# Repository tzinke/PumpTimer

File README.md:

<p>A timer for my pool pump using a Raspberry Pi Zero W and a custom-made PCB.</p>

# Pool Pump Timer Instructions

<p>This device emits its own wi-fi network which will allow you to connect to the controller and set schedules and toggle the pump on/off.</p>

<p>The name of the network is PumpController, and the password is PumpController2803Pool</p>
  
<p>This network is NOT connected to the internet, so you'll probably want to deselect auto-connect for this network (otherwise your device might automatically hop on this network and not be connected to the internet). To control the device, you will also need to turn cell data off if connecting with a phone.</p>

<p>Once connected, open a browser and navigate to pumpcontroller.com. This will pull up the controller interface.</p>

<p>Here, you can set a schedule to turn the pump on/off at the same time each day, set the on-board clock, set a "one-time run" (a schedule that will only execute a single time, after which the daily schedule will resume), toggle the pump on/off manually, and view logs from the last 3 months.
The on-board clock is very accurate with little drift, but it is not configured to automatically adjust for daylight savings.</p>

<p>The device is also configured to turn the pump on for at least 10 minutes if the temperature gets too close to 32F in order to prevent equipment damage from freezes.
The on-board temperature sensor isn't terribly accurate, so there is an adjustment factor that you can change to get it more accurate/modify the "freeze" threshold.</p>

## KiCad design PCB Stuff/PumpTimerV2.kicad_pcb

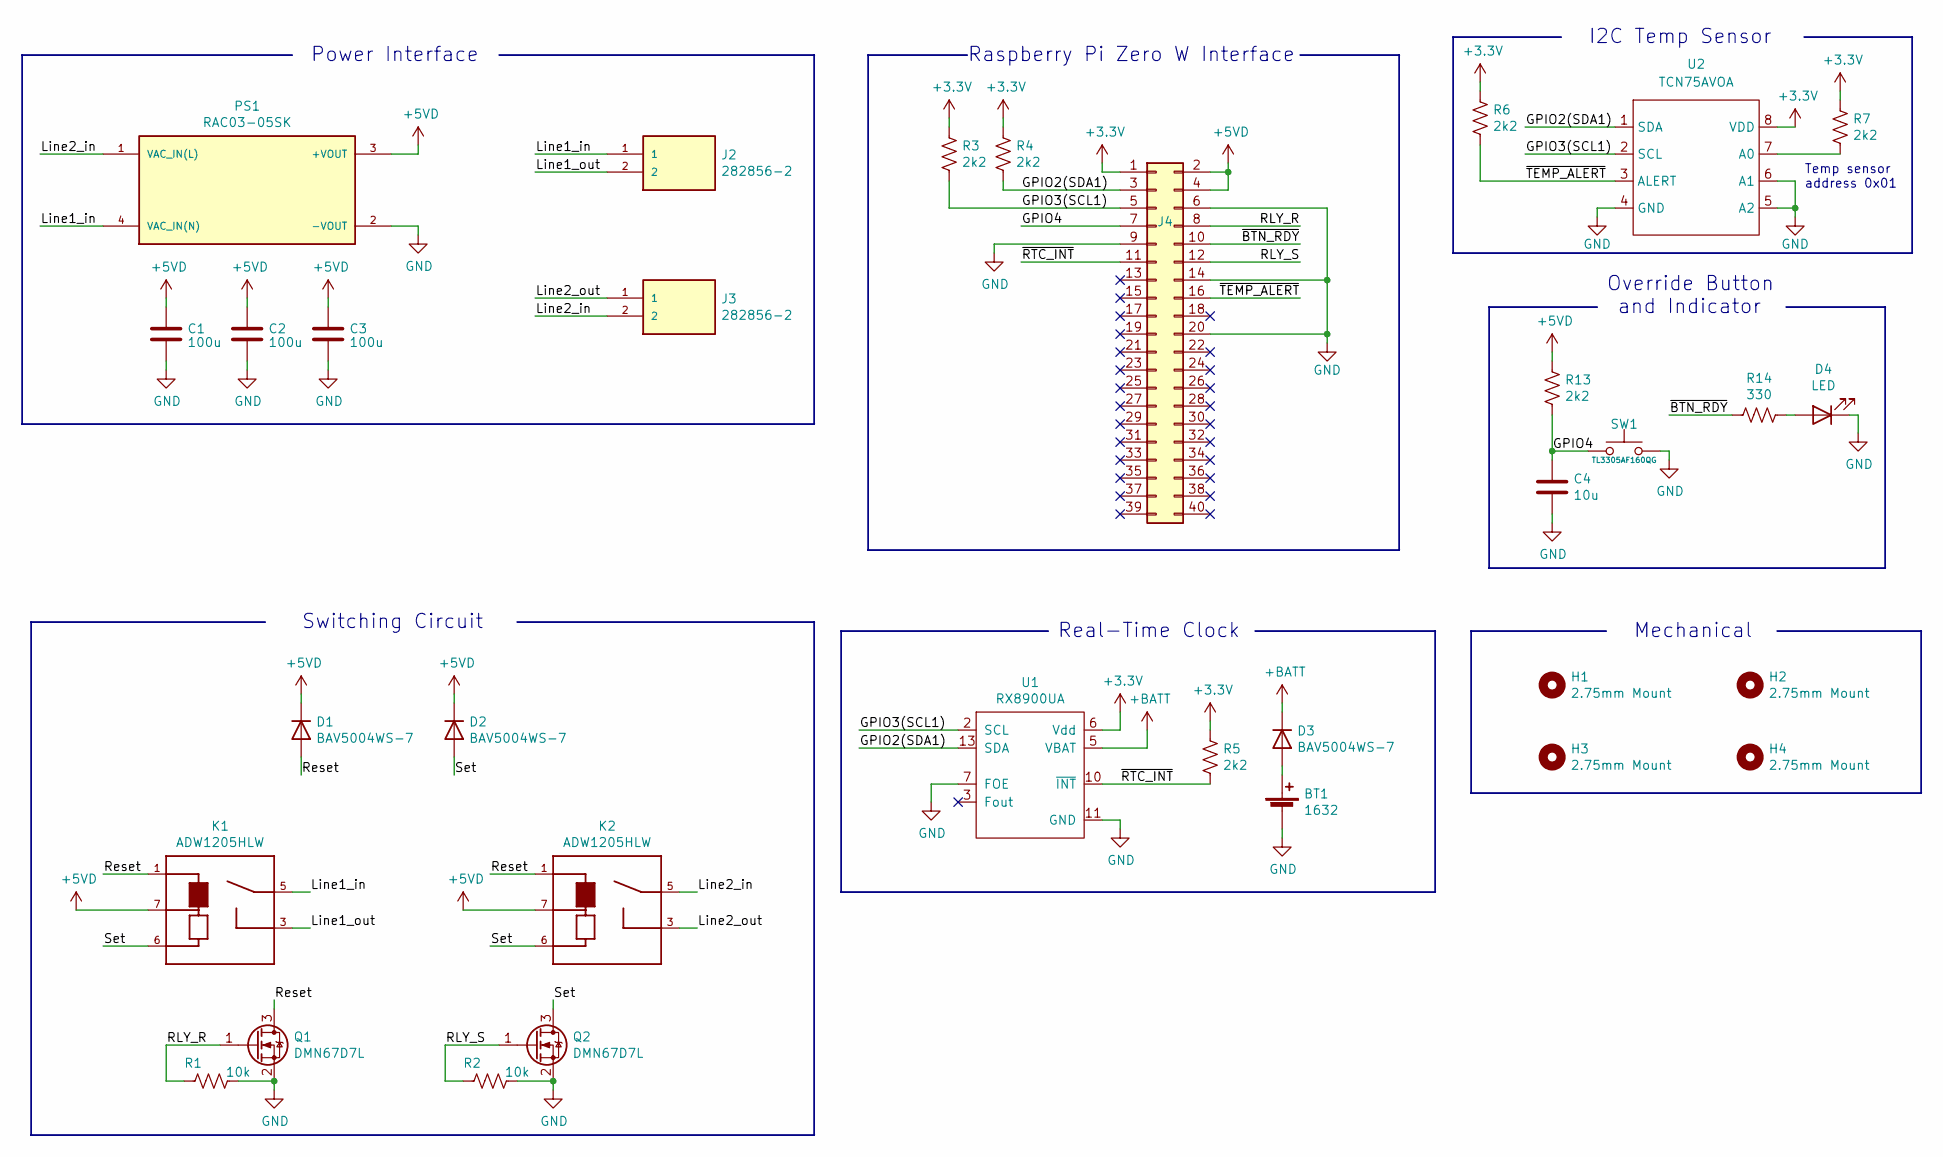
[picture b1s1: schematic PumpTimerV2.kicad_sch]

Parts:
BT1: 1632; Vertical_16mm_coin_holder; Part Keystone 1069
C1, C2, C3: 100u; C_1206_3216Metric_Pad1.33x1.80mm_HandSolder; Part GMC31X5R107M10NT
C4: 10u; C_0603_1608Metric_Pad1.08x0.95mm_HandSolder; Part LMK107BJ106MALTD
D1, D2, D3: BAV5004WS-7; D_SOD-323; Part BAV5004WS-7
D4: LED; LED_0603_1608Metric_Castellated; Part SML-D12U1WT86
H1, H2, H3, H4: 2.75mm Mount; MountingHole_2.7mm_M2.5; Part 50M025045G008
J2, J3: 282856-2; TE_282856-2; Part 282856-2
J4: Conn_02x20_Odd_Even; PinHeader_2x20_P2.54mm_Vertical; Part M20-9982046
K1, K2: ADW1205HLW; RELAY_ADW1205HLW; Part ADW1205HLW
PS1: RAC03-05SK; Part RAC03-05SK
Q1, Q2: DMN67D7L; SOT-23; Part DMN67D7L
R1, R2: 10k; R_0603_1608Metric_Pad0.98x0.95mm_HandSolder; Part ERJ-PA3J103V
R3, R4, R5, R6, R7, R13: 2k2; R_0603_1608Metric_Pad0.98x0.95mm_HandSolder; Part CRGP0603F2K2
R14: 330; R_0603_1608Metric_Pad0.98x0.95mm_HandSolder; Part CRGCQ0603F330R
SW1: TL3305AF160QG; Part TL3305AF160QG
U1: RX8900UA; SOP-14_127P780x200; Part RX8900UA
U2: TCN75AVOA; SOIC-8_3.9x4.9mm_P1.27mm

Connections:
+3V3: J4.1, R3.1, R4.1, R5.1, R6.1, R7.1, U1.6 (Vdd), U2.8 (VDD)
+5VD: C1.1, C2.1, C3.1, D1.2 (K), D2.2 (K), J4.2, J4.4, K1.7, K2.7, PS1.3 (+VOUT), R13.1
+BATT: D3.2 (K), U1.5 (VBAT)
/GPIO2(SDA1): J4.3, R4.2, U1.13 (SDA), U2.1 (SDA)
/GPIO3(SCL1): J4.5, R3.2, U1.2 (SCL), U2.2 (SCL)
/GPIO4: C4.1, J4.7, R13.2, SW1.1
/Line1_in: J2.1, K1.5, PS1.4 (VAC_IN(N))
/Line1_out: J2.2, K1.3
/Line2_in: J3.2, K2.5, PS1.1 (VAC_IN(L))
/Line2_out: J3.1, K2.3
/RLY_R: J4.8, Q1.1 (G), R1.2
/RLY_S: J4.12, Q2.1 (G), R2.2
/Reset: D1.1 (A), K1.1, K2.1, Q1.3 (D)
/Set: D2.1 (A), K1.6, K2.6, Q2.3 (D)
/~BTN_RDY: J4.10, R14.2
/~RTC_INT: J4.11, R5.2, U1.10 (~INT)
/~TEMP_ALERT: J4.16, R6.2, U2.3 (ALERT)
GND: BT1.NEG (-), C1.2, C2.2, C3.2, C4.2, D4.1 (K), J4.6, J4.9, J4.14, J4.20, PS1.2 (-VOUT), Q1.2 (S), Q2.2 (S), R1.1, R2.1, SW1.2, U1.7 (FOE), U1.11 (GND), U2.4 (GND), U2.5 (A2), U2.6 (A1)
unnamed: BT1.POS (+), D3.1 (A)
unnamed: D4.2 (A), R14.1
unnamed: R7.2, U2.7 (A0)

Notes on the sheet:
Override Button and Indicator
Mechanical
Switching Circuit
I2C Temp Sensor
Raspberry Pi Zero W Interface
Power Interface
Real-Time Clock
Temp sensor address 0x01

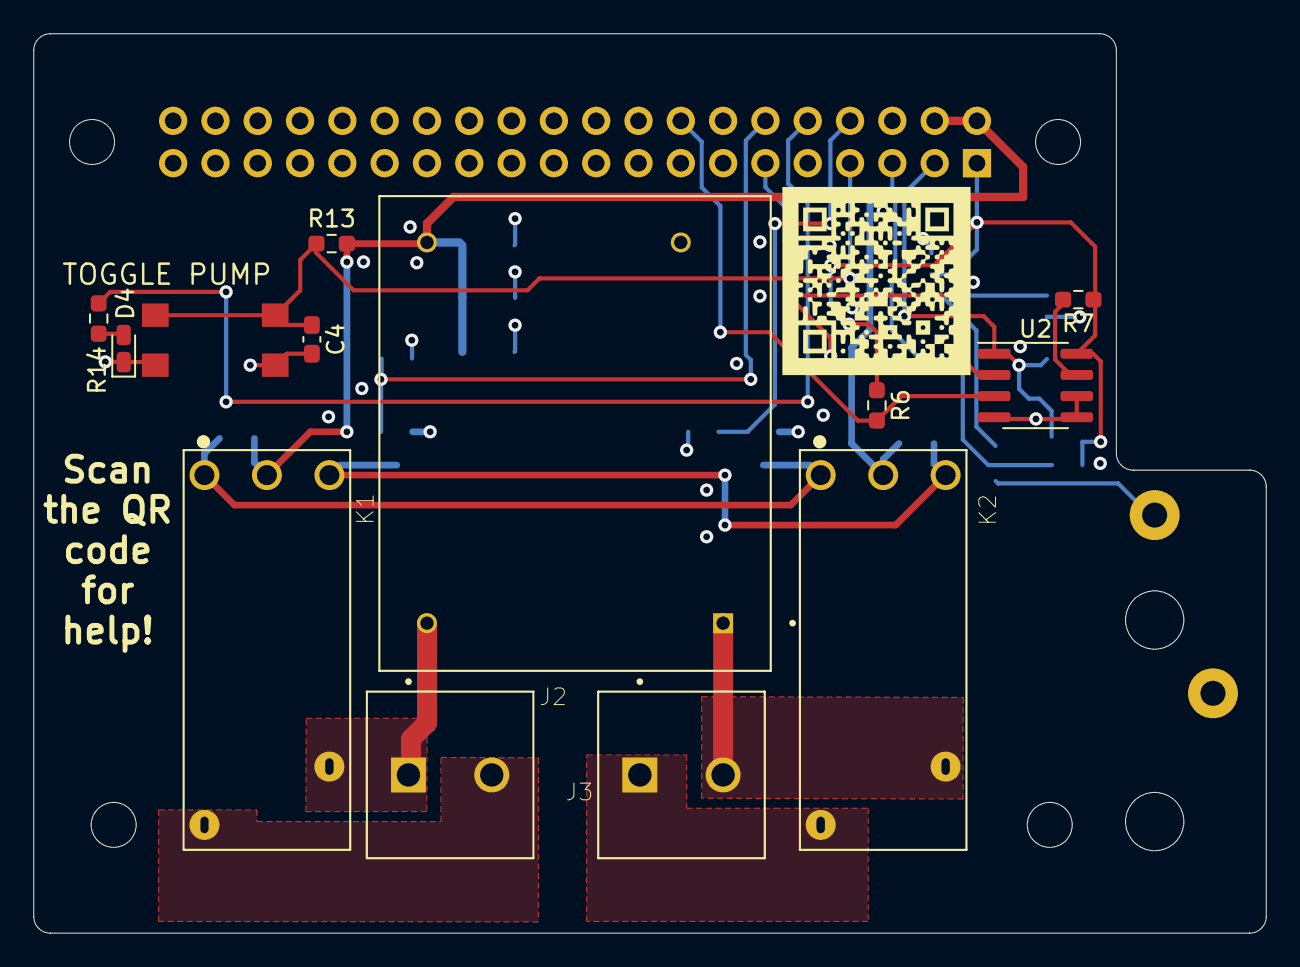
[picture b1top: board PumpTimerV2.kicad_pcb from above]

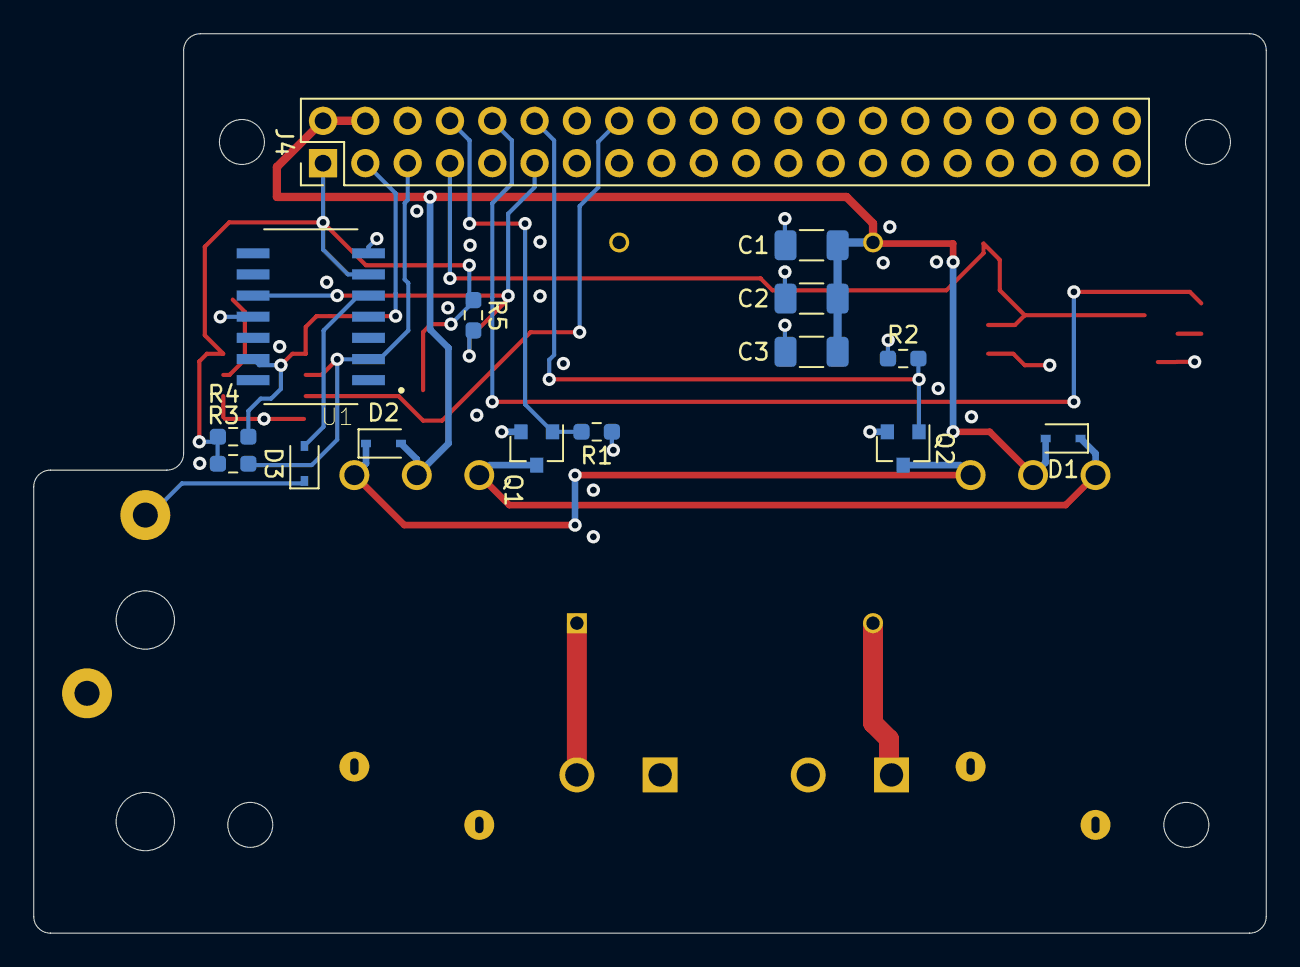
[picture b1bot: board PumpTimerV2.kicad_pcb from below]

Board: 4 copper layers, 74.0 x 54.0 mm, 33 parts (15 on the bottom side), 21 nets.

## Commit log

2020-03-17 Uploading 3D PCB and schematic/2D PCB
2020-03-17 Adding main.c
2020-03-17 Adding microcontroller code
2020-03-17 Created PCB Stuff folder
2020-03-17 Adding PCB PDFs. Download PCB1.pdf to view
2020-03-17 3D PCB model. Use Acrobat Reader to view.
2020-03-17 PCB and electrical schematic
2020-03-17 Fixed microcontroller pins in schematic
2020-03-17 Fixed pin numbers, increased relay actuation timing
2020-03-19 Changed pump's run-time pattern
    Previous version had pump's run-time dispersed symmetrically over 24 hours. I read online that running the pump at night isn't very useful, so this version runs the pump evenly over 12 hours (aimed a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
2020-04-03 Added override feature
2020-04-07 Deleting unnecessary file
2020-04-07 Code clean-up, reenabling interrupts after disable
    Forgot to re-enable the interrupts once they had been disabled by a short-press of rst button.
2020-04-07 Fixed error in on-off pattern calculation
    Had odd-runtime pattern running half_runtime_hours too long
2020-04-12 Fixed reset & override functions, decluttered code
2020-04-12 Create images folder
2020-04-12 Added pictures of buttons
2020-04-12 Tinkered with timing to get it more accurate
2020-04-12 Tinkered with timing to make it more accurate
2020-04-16 Added drift correction, removed on-off-on pattern
    I'm not convinced the pattern made sense. Seems like shifting the run-time back in the day and having it run without discontinuity would leave the least amount of heat + direct sun in the pool, thus 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
2020-04-16 Change drift correction, improve override function
2020-04-26 Update to drift correction
2020-06-12 Re-defined button functions and timer-overriding
2020-07-13 Fixed some logic errors
    Timed pump state was only being set if the timer wasn't overridden in the increment/decrement functions. It should be set regardless. It was also only being set in the checktime function if in an ove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
2021-02-02 Code clean-up/debug
    De-override wasn't returning system to proper timed state. Changed to explicitly set/check control variables to 1 or 0.
2021-04-13 Adding KiCad documents
2021-04-14 Adding button interface + LED indicator for manual switching of pump state
2021-04-15 Beginning layout. Removed a few non-critical components that will not fit.
2021-04-15 Temoprarily adding 3D models, removing stuff in PCB layout
2021-04-15 Same as last. Need to flip RPI and connector. Line up for mounting.
2021-04-15 Clean-up, changing board size + adding bigger header for rpi
2021-04-19 Work on PCB layout
2021-04-20 Start routing
2021-04-21 Routing and placement
2021-04-21 Finished placement and routing. Everything needs reviewed.
2021-04-21 Moving battery holder onto tab. Need to add mounting holes at bottom of board and review.
2021-04-22 Adding QR code
2021-04-22 Adding old pcb files (Altium)
2021-04-22 Slight rearranging, changing neutral screw terminal to higher-current model
2021-04-23 Raspberry Pi header was backwards... Needs rerouted.
2021-04-23 Started re-routing after flipping rpi header
2021-04-23 Making sure schematic and PCB match. Finished re-routing after flipping rpi header.
2021-04-24 Potentially final routing & review. Might check things over one more time before submitting for fab
2021-04-26 Moving things around to have bigger traces on the AC lines
2021-04-27 Finished routing bigger AC-line traces
2021-04-28 Adding BOM
2021-05-10 Removing obsolete microcontroller code, adding initial web interface files
2021-05-11 Defined some of the file paths and schedule-file behavior
2021-05-12 Deleted obsolete README instructions
2021-05-13 Adding (incomplete) rtc code
2021-05-14 Defined RTC functions, a few more flask functions
2021-05-14 Updating the webpage templates
2021-05-17 Adding mounting plate (maybe shouldn't be part of the main project since it's specific to my enclosure)
2021-05-18 Added GPIO setup
2021-05-19 Initial definition of task schedule
2021-05-19 Cleaning up unused imports, place-holder functions, etc.
2021-05-20 Adding cooldown and mutex to app structure. Defined checktime function
2021-05-21 Further development in app.py
2021-05-26 Correcting RTC.py functions
2021-06-14 Changing "mutex" behavior for button function
2021-06-15 Adding drift correction for PT task, commenting out PT stuff until it's installed into system
2021-06-15 Minor additions to scheduling functions. Both are still incomplete.
2021-06-17 Fixing scheduling functions, rtc_set(), error handling, changed timer task function
2021-06-18 Adding state-change timestamp variable
2021-06-21 Fixed rtc function calls.
2021-06-21 Fixing syntax errors, incorrect css link
2021-06-21 Moving away from bootstrap and using custom stylization
2021-06-22 Adding css file, moving rtc functions into app.py, adding setSchedule, custom buttons in html pages
2021-06-23 Fixing current time displayed on pages, minor bugs
2021-06-23 Fixing schedule behaviors for schedule change, system time change, and system boot
2021-06-29 Adding setOneTime.html, adding some logic for scheduling to app.py
2021-06-29 I think things got out of sync. Just getting back to a functional state for daily schedules
2021-07-06 Adding a TODO so I don't forget to switch to a true mutex
2021-07-23 Various fixes. Improving schedule logic, html issues.
2021-07-23 Minor updates to schedule logic
2021-07-24 Switching mutex to threading.Lock
2021-07-25 Adding some logging features (not complete)
2021-07-31 Fixed issue with one-time-run setting. Need to test setting a new one-time schedule when the pump is on outside of said schedule
2021-08-01 Fixing info on main page. Attempting to fix /toggle bug, but it's still giving errors. Need to return main.html when user navigates to /toggle
2021-08-01 Added event logging. Tried fixing event-time reporting for /main. Tried fixing /toggle.
2021-08-03 Fixed syntax error, log_path wasn't declared global in checkTime
2021-08-03 Adding block to remove an old log (the one from 3 months ago) when a new log is created
2021-08-15 appToggle() was throwing an error without a return statement. Copied main()'s code into appToggle()
2021-10-13 Updated setTime page to have a single entry box
2021-10-13 Using the web toggle button will now redirect to / instead of leaving /toggle in the address bar.
2022-05-07 Updating time entries to use HTML time and datetime input types
2023-02-16 Removed "Neutral" net (my AC/DC converter died. Seems like 230V input is nominal anyways)
2023-02-16 Added temp sensor. Started adding to PCB but not yet placed or routed.
2023-03-01 Rerouted PCB with temp sensor in place
2023-03-13 Fixed page width on mobile
2023-04-27 Added temp sensor operations
2023-05-01 Update pump state logic
2023-05-02 Fixed some issues found while testing freeze protection. Fixed log deletion.
2023-05-02 Added page to change temp sensor settings
2023-05-04 Got log retrieval working
2023-05-04 Made current date easier to read
2023-05-10 Fixed a few issues in web toggle callback
